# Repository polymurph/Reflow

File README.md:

# Reflow

## How to Contribute

source: https://www.youtube.com/watch?v=CML6vfKjQss

1. fork the project

2. make a new brachnch in the forked project

3. programm your features

3. one you are done go to your fork on github and hit the "compare & pull request" button

4. describe the feature, adaptation, bugfix or etc.

5. when done with documenting hit the "create pull request" button. 

## README Creation tipps

https://www.youtube.com/watch?v=E6NO0rgFub4

## Git Submodules

source: https://devconnected.com/how-to-add-and-update-git-submodules/

### Adding git submodule¨

-> https://stackoverflow.com/questions/43761594/cmake-and-using-git-submodule-for-dependence-projects

```
git submodule add <remote_url> <destination_folder>
git commit -m "Added the submodule to the project."
git push
```

### update git submodule

```
git submodule update --init --recursive
```

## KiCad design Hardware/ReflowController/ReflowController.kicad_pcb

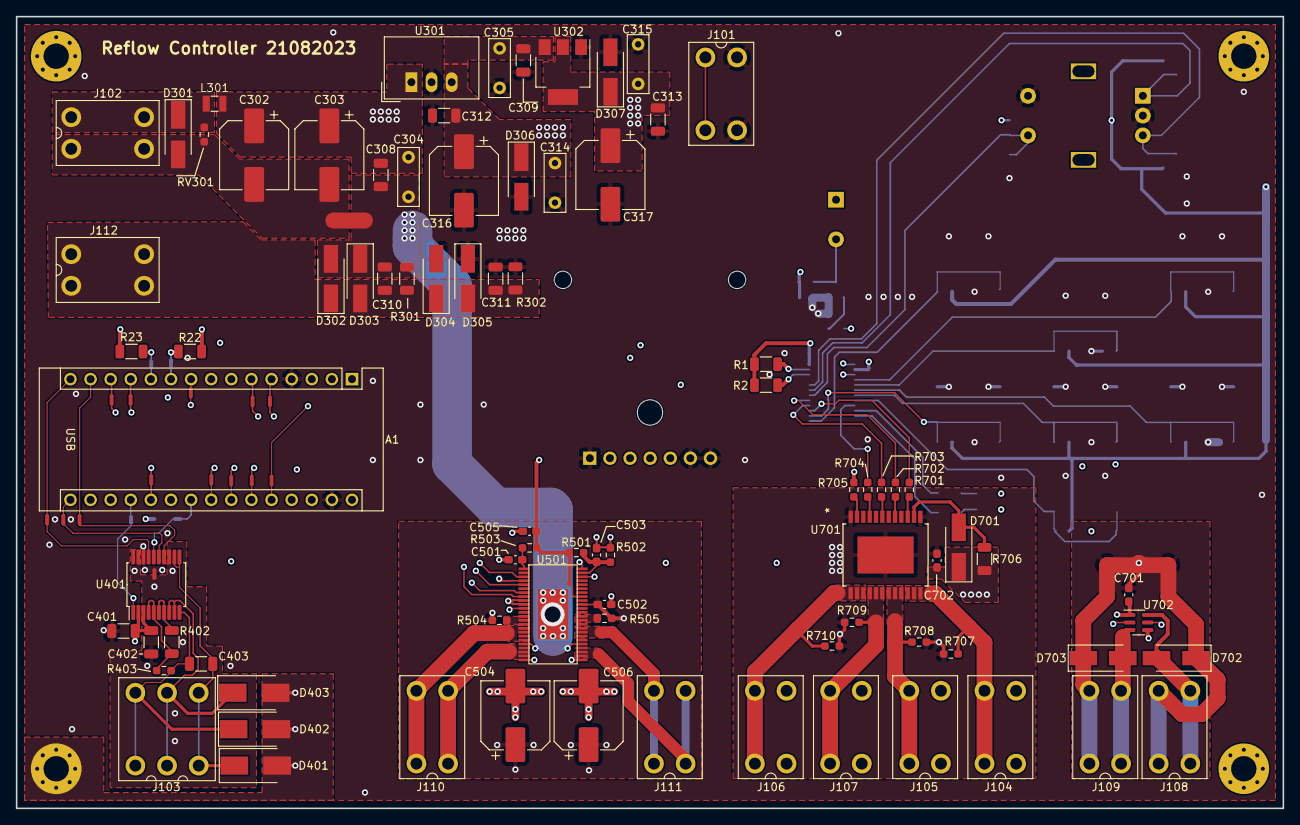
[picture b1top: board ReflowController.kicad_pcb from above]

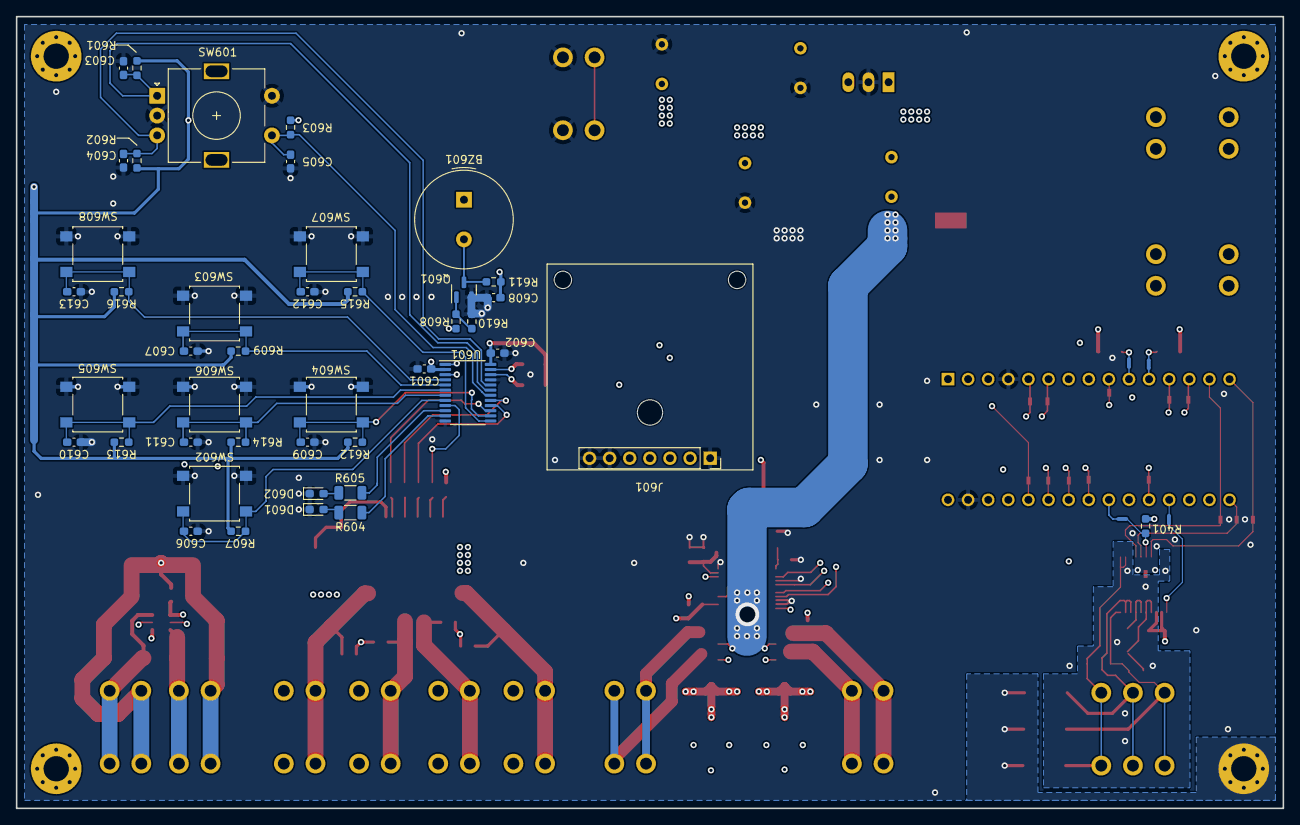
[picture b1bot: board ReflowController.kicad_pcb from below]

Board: 4 copper layers, 160.0 x 100.0 mm, 153 parts (47 on the bottom side), 90 nets.

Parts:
A1: NUCLEO_STM32F042K6; Arduino_Nano
BZ601: Buzzer; Buzzer_TDK_PS1240P02BT_D12.2mm_H6.5mm
C302, C303, C316, C317, C504, C506: 100uF; CP_Elec_8x10.5
C304, C305, C314, C315: 0.1uF; C_Rect_L7.2mm_W2.5mm_P5.00mm_FKS2_FKP2_MKS2_MKP2
C308, C309, C310, C311, C312, C313, C401, C402: 0.1uF; C_1206_3216Metric
C403: 10n; C_1206_3216Metric
C501: 270pF; C_0603_1608Metric_Pad1.08x0.95mm_HandSolder
C502, C503, C505, C601, C602, C603, C604, C605, C606, C607, C608, C609, C610, C611, C612, C613, C701, C702: 0.1uF; C_0603_1608Metric_Pad1.08x0.95mm_HandSolder
D301, D302, D303, D304, D305, D306, D307, D702, D703: SBRT; D_SMA_Handsoldering
D401, D402, D403: SMLVT3V3; D_SMB_Handsoldering
D601: RED; LED_0603_1608Metric_Pad1.05x0.95mm_HandSolder
D602: GREEN; LED_0603_1608Metric_Pad1.05x0.95mm_HandSolder
D701: RSFJL; D_SMA_Handsoldering
H101, H102, H103, H104: Mount; MountingHole_3.2mm_M3_Pad_Via
H105: Mount; MountingHole_3.2mm_M3
H106, H107: LCD_Mount; MountingHole_2.2mm_M2_ISO7380
J101, J102, J104, J105, J106, J107, J108, J109, J110, J111, J112: 2060-1452; wago_2060-1452
J103: 2060-1453; wago_2060-1453
J601: LCD_HEADER; PinSocket_1x07_P2.54mm_Vertical
L301: 470nH; 2520
NT1, NT2, NT3, NT4, NT5, NT6, NT7, NT8, NT9, NT10, NT11, NT12, NT13, NT14, NT15, NT16, NT17, NT402: NetTie_2; NetTie-2_SMD_Pad0.5mm
NT301, NT701, NT702: NetTie_2; NetTie-2_SMD_Pad2.0mm
Q601: BC848; SOT-23
R1, R2, R22, R23, R604, R605: 4k7; R_1206_3216Metric
R301, R302: 10M; R_1206_3216Metric
R401, R501, R502, R601, R602, R603, R607, R609, R610, R612, R613, R614, R615, R616, R701, R702, R703, R704, R705, R707, R708, R709, R710: 10k; R_0603_1608Metric_Pad0.98x0.95mm_HandSolder
R402: 402; R_1206_3216Metric
R403: 10M; R_0603_1608Metric_Pad0.98x0.95mm_HandSolder
R503: 5.1K; R_0603_1608Metric_Pad0.98x0.95mm_HandSolder
R504, R505: 0.22R; R_0603_1608Metric_Pad0.98x0.95mm_HandSolder
R608, R611: 1k; R_0603_1608Metric_Pad0.98x0.95mm_HandSolder
R706: 0R; R_1206_3216Metric
RV301: AVR; R_0603_1608Metric_Pad0.98x0.95mm_HandSolder
SW601: RotaryEncoder_Switch; RotaryEncoder_Alps_EC11E-Switch_Vertical_H20mm
SW602: SW_UP; SW_SPST_B3S-1000
SW603: SW_DOWN; SW_SPST_B3S-1000
SW604: SW_LEFT; SW_SPST_B3S-1000
SW605: SW_RIGHT; SW_SPST_B3S-1000
SW606: SW_SELECT; SW_SPST_B3S-1000
SW607: SW_RET; SW_SPST_B3S-1000
SW608: SW_RESET; SW_SPST_B3S-1000
U301: TSR_1-2450; Converter_DCDC_TRACO_TSR-1_THT
U302: LD1117S33TR_SOT223; SOT-223-3_TabPin2
U401: MAX31865xAP; SSOP-20_5.3x7.2mm_P0.65mm
U501: TB67H400AFNG; HTSSOP48
U601: PI4IOE5V6416; TSSOP-24_4.4x7.8mm_P0.65mm
U701: VNQ5160K-E
U702: SZNUD3124DMT1G; SC-74-6_1.5x2.9mm_P0.95mm

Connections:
+3.3V: A1.17 (3V3), BZ601.1 (-), C313.2, C315.1, C317.1, C401.2, C402.1, C601.1, C602.1, C608.1, D307.1 (K), J601.2, R1.1, R2.1, R22.1, R23.1, R401.2, R601.2, R602.1, R603.2, R607.2, R609.2, R611.1, R612.2, R613.2, R614.2, R615.2, R616.2, R705.2, U302.2 (VO), U401.2 (DVDD), U401.3 (VDD), U601.2 (VDD), U601.24 (VDDP)
+5V: A1.27 (+5V), C305.1, C309.2, C312.2, C314.1, C316.1, C505.1, D306.1 (K), R501.2, R503.2, U301.3 (Vout), U302.3 (VI), U501.41 (VCC)
+24V: C302.1, C303.1, C304.1, C308.2, C502.1, C504.1, C506.1, C701.1, C702.1, L301.2, NT701.1, NT702.1, R504.2, R505.2, R707.2, R708.2, R709.2, R710.2, U301.1 (Vin), U501.39 (VM), U701.1 (VCC), U701.12 (VCC), U701.EPAD (VCC)
/BUZZER_PWM: NT6.2, R608.1
/FAN_1_EN: NT12.2, U501.3 (INA1)
/FAN_1_PWM: NT13.2, U501.5 (PWMA)
/FAN_2_EN: NT14.2, U501.8 (INB1)
/FAN_2_PWM: NT15.2, U501.7 (PWMB)
/Fan Driver/FAN_1_OUT_+: J110.1, U501.16 (OUTA+), U501.17 (OUTA+)
/Fan Driver/FAN_1_OUT_-: J110.2, U501.22 (OUTA-), U501.23 (OUTA-)
/Fan Driver/FAN_2_OUT_+: J111.1, U501.32 (OUTB+), U501.33 (OUTB+)
/Fan Driver/FAN_2_OUT_-: J111.2, U501.26 (OUTB-), U501.27 (OUTB-)
/HSS_1_EN: R701.1, U601.15 (P1_2)
/HSS_2_EN: R703.1, U601.16 (P1_3)
/HSS_3_EN: R702.1, U601.17 (P1_4)
/HSS_4_EN: R704.1, U601.9 (P0_5)
/IO/HSS_1_OUT_+: J104.1, R707.1, U701.22 (OUTPUT1), U701.23 (OUTPUT1), U701.24 (OUTPUT1)
/IO/HSS_2_OUT_+: J105.1, R708.1, U701.19 (OUTPUT2), U701.20 (OUTPUT2), U701.21 (OUTPUT2)
/IO/HSS_3_OUT_+: J107.1, R709.1, U701.16 (OUTPUT3), U701.17 (OUTPUT3), U701.18 (OUTPUT3)
/IO/HSS_4_OUT_+: J106.1, R710.1, U701.13 (OUTPUT4), U701.14 (OUTPUT4), U701.15 (OUTPUT4)
/IO/relay_1_coil_+: D702.1 (K), J108.1, NT701.2
/IO/relay_1_coil_-: D702.2 (A), J108.2, U702.6 (Drain_1)
/IO/relay_2_coil_+: D703.1 (K), J109.1, NT702.2
/IO/relay_2_coil_-: D703.2 (A), J109.2, U702.3 (Drain_2)
/MISO: NT2.2, U401.17 (SDO)
/MOSI: NT1.2, U401.14 (SDI)
/PSU/24V_GND_IN: C302.2, C303.2, D301.2 (A), J102.2, NT301.1, RV301.2
/PSU/+24V_IN: D301.1 (K), J102.1, L301.1, RV301.1
/RELAY_1_EN: NT9.2, U702.2 (Gate_1)
/RELAY_2_EN: NT10.2, U702.5 (Gate_2)
/SCL: J601.3, NT5.2, R2.2, R23.2, U601.22 (SCL)
/SCLK: NT3.2, U401.15 (SCLK)
/SDA: J601.4, NT4.2, R1.2, R22.2, U601.23 (SDA)
/TemperatureReader/PT100_+IN: C403.2, D402.1 (K), J103.1, R403.1, U401.10 (RTDIN+)
/TemperatureReader/PT100_+OUT: D403.1 (K), J103.2, U401.8 (FORCE+), U401.9 (FORCE2)
/TemperatureReader/PT100_-IN: C403.1, D401.1 (K), J103.3, U401.11 (RTDIN-), U401.12 (FORCE-)
/TemperatureReader/REFIN+: R402.1, R403.2, U401.4 (BIAS), U401.5 (REFIN+)
/TemperatureReader/REFIN-: R402.2, U401.6 (REFIN-), U401.7 (ISENSOR)
/TemperatureReader/T_AGND: C402.2, NT402.2, U401.13 (GND), U401.19 (GND)
/uC/PA0: A1.19 (A0), NT16.1
/uC/PA1: A1.20 (A1), NT11.1
/uC/PA2: A1.26 (A7), NT8.1
/uC/PA4: A1.22 (A3), NT17.1
/uC/PA5: A1.23 (A4), NT6.1
/uC/PA6: A1.24 (A5), NT14.1
/uC/PA7: A1.25 (A6), NT12.1
/uC/PA8: A1.12 (D9), NT9.1
/uC/PA11: A1.13 (D10), NT10.1
/uC/PA12: A1.5 (D2), NT7.1
/uC/PB0: A1.6 (D3), NT13.1
/uC/PB1: A1.9 (D6), NT15.1
/uC/PB3: A1.16 (D13), NT3.1
/uC/PB4: A1.15 (D12), NT2.1
/uC/PB5: A1.14 (D11), NT1.1
/uC/PF0: A1.10 (D7), NT4.1
/uC/PF1: A1.11 (D8), NT5.1
/uC/~INT_EMERGENCY_STOP: J101.2, NT8.2
/ui/BTN_DOWN: C607.1, R609.1, SW603.2, U601.5 (P0_1)
/ui/BTN_LEFT: C609.1, R612.1, SW604.2, U601.14 (P1_1)
/ui/BTN_RESET: C613.1, R616.1, SW608.2, U601.4 (P0_0)
/ui/BTN_RET: C612.1, R615.1, SW607.2, U601.13 (P1_0)
/ui/BTN_RIGHT: C610.1, R613.1, SW605.2, U601.6 (P0_2)
/ui/BTN_SELECT: C611.1, R614.1, SW606.2, U601.7 (P0_3)
/ui/BTN_UP: C606.1, R607.1, SW602.2, U601.8 (P0_4)
/ui/ENCODER_A: C603.1, R601.1, SW601.A, U601.19 (P1_6)
/ui/ENCODER_B: C604.1, R602.2, SW601.B, U601.20 (P1_7)
/ui/ENCODER_SW: C605.1, R603.1, SW601.S1, U601.18 (P1_5)
/ui/LED_ALIVE: R605.1, U601.10 (P0_6)
/ui/LED_ERROR: R604.1, U601.11 (P0_7)
/~CS_TEMP: NT17.2, R401.1, U401.16 (~CS)
/~IO_INT: NT11.2, U601.1 (~INT)
/~TMP_RDY: NT16.2, U401.1 (~DRDY)
/~UI_RESET: J601.5, NT7.2, U601.3 (~RESET)
Earth: C310.1, C311.1, D302.1 (K), D303.2 (A), D304.1 (K), D305.2 (A), D401.2 (A), D402.2 (A), D403.2 (A), H101.1, H102.1, J112.1, J112.2, R301.2, R302.2
GND: A1.4 (GND), A1.29 (GND), C305.2, C309.1, C311.2, C312.1, C313.1, C314.2, C315.2, C316.2, C317.2, C401.1, C501.2, C503.2, C505.2, C601.2, C602.2, C603.2, C604.2, C605.2, C606.2, C607.2, C608.2, C609.2, C610.2, C611.2, C612.2, C613.2, D304.2 (A), D305.1 (K), D306.2 (A), D307.2 (A), D601.1 (K), D602.1 (K), J101.1, J601.1, J601.6, J601.7, NT402.1, Q601.2 (E), R302.1, R502.1, R610.1, SW601.C, SW601.S2, SW602.1, SW603.1, SW604.1, SW605.1, SW606.1, SW607.1, SW608.1, U301.2 (GND), U302.1 (GND), U401.18 (DGND), U501.4 (INA2), U501.9 (INB2), U501.10 (TBLKAB), U501.48 (HBMODE), U601.12 (VSS), U601.21 (ADDR)
GNDPWR: C304.2, C308.1, C310.2, C502.2, C504.2, C506.2, C701.2, C702.2, D302.2 (A), D303.1 (K), D701.1 (K), J104.2, J105.2, J106.2, J107.2, NT301.2, R301.1, R706.2, U501.11 (GND), U501.20 (GND), U501.24 (GND), U501.25 (GND), U501.29 (GND), U501.46 (GND), U501.PAD (GND), U702.1 (Source_1), U702.4 (Source_2)
unnamed: BZ601.2 (+), Q601.3 (C), R611.2
unnamed: D601.2 (A), R604.2
unnamed: D602.2 (A), R605.2
unnamed: D701.2 (A), R706.1, U701.2 (GND)
unnamed: Q601.1 (B), R608.2, R610.2
unnamed: R504.1, U501.13 (RSA), U501.14 (RSA)
unnamed: R505.1, U501.35 (RSB), U501.36 (RSB)
unnamed: C501.1, R503.1, U501.1 (OSCM)
unnamed: C503.1, R501.1, R502.2, U501.47 (VREF)
unnamed: R701.2, U701.3 (INPUT1)
unnamed: R702.2, U701.5 (INPUT2)
unnamed: R703.2, U701.7 (INPUT3)
unnamed: R704.2, U701.9 (INPUT4)
unnamed: R705.1, U701.11 (STAT_DIS)

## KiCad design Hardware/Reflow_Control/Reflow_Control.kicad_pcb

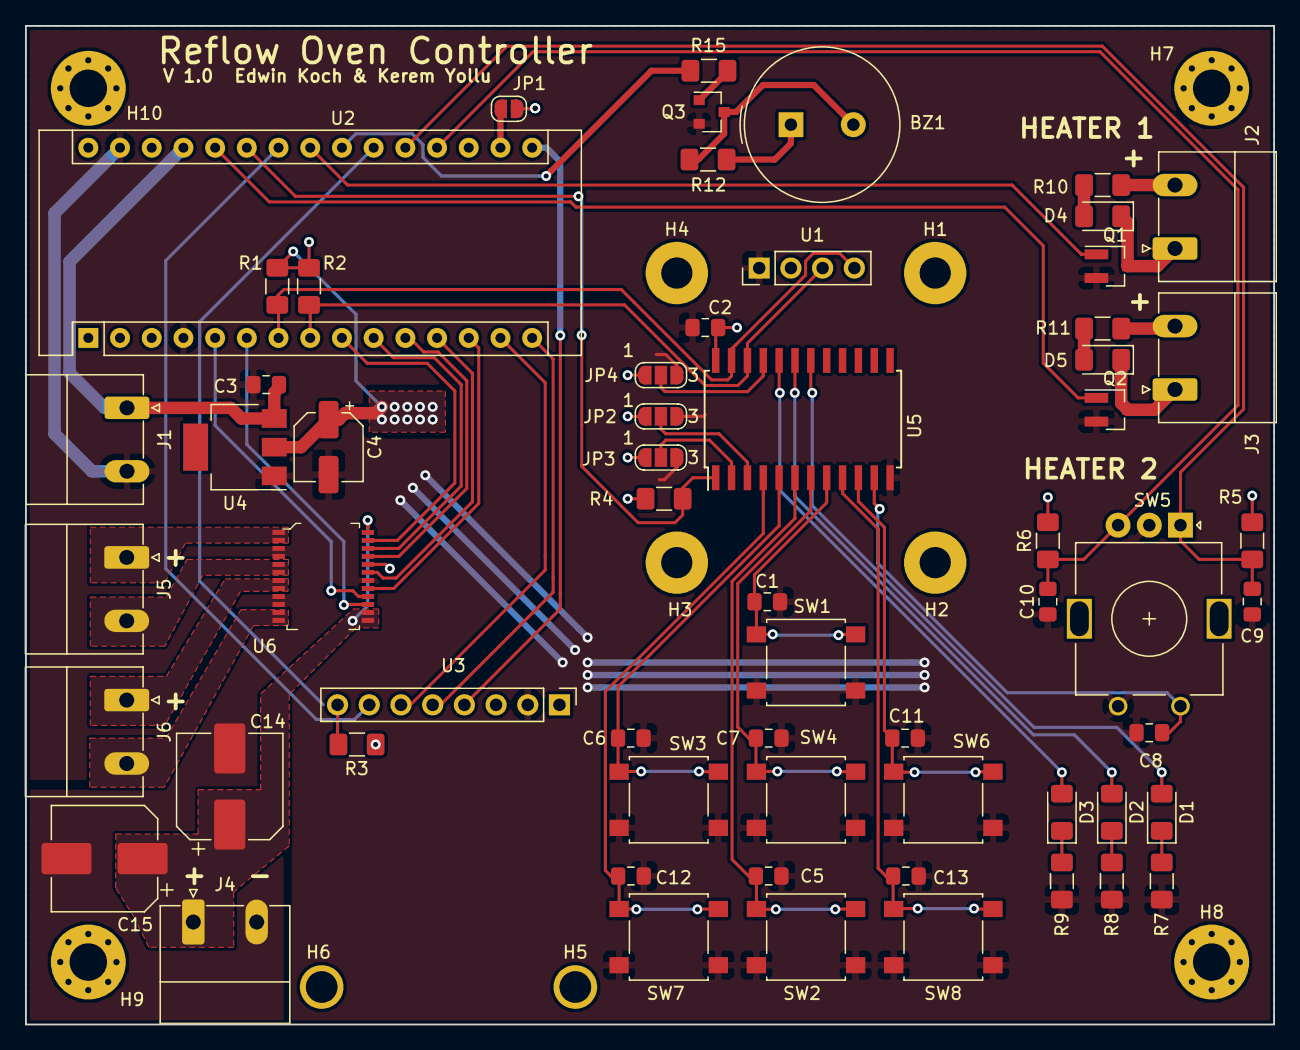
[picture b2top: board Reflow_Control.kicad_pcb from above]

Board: 2 copper layers, 100.0 x 80.0 mm, 71 parts (0 on the bottom side), 52 nets.

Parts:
BZ1: Buzzer; Buzzer_TDK_PS1240P02BT_D12.2mm_H6.5mm
C1, C3, C5, C6, C7, C8, C9, C10, C11, C12, C13: 10uF; C_0805_2012Metric_Pad1.15x1.40mm_HandSolder
C2: 100n; C_0805_2012Metric_Pad1.15x1.40mm_HandSolder
C4: 100uF; CP_Elec_5x5.4
C14, C15: 100uF; CP_Elec_8x6.2
D1, D2, D3, D4, D5: LED; LED_1206_3216Metric_Pad1.42x1.75mm_HandSolder
H1, H2, H3, H4, H5, H6: MountingHole; MountingHole_2.5mm_Pad
H7, H8, H9, H10: MountingHole; MountingHole_3mm_Pad_Via
J1: Conn_5V; PhoenixContact_MC_1,5_2-G-5.08_1x02_P5.08mm_Horizontal
J2: Conn_ssr_1; PhoenixContact_MC_1,5_2-G-5.08_1x02_P5.08mm_Horizontal
J3: Conn_ssr_2; PhoenixContact_MC_1,5_2-G-5.08_1x02_P5.08mm_Horizontal
J4: Conn_mot_PWR; PhoenixContact_MC_1,5_2-G-5.08_1x02_P5.08mm_Horizontal
J5: Conn_mot_1; PhoenixContact_MC_1,5_2-G-5.08_1x02_P5.08mm_Horizontal
J6: Conn_mot_2; PhoenixContact_MC_1,5_2-G-5.08_1x02_P5.08mm_Horizontal
JP1: 3.3V Jumper; SolderJumper-2_P1.3mm_Open_RoundedPad1.0x1.5mm
JP2, JP3, JP4: ADDR_A2; SolderJumper-3_P1.3mm_Open_RoundedPad1.0x1.5mm_NumberLabels
Q1: Q_NMOS_GSD; SOT-23_Handsoldering
Q2: NUD3112LT1G; SOT-23_Handsoldering
Q3: BC848; SOT-23
R1, R2, R3, R4, R5, R6, R7, R8, R9: 4k7; R_1206_3216Metric_Pad1.42x1.75mm_HandSolder
R10, R11, R12, R15: 1k; R_1206_3216Metric_Pad1.42x1.75mm_HandSolder
SW1, SW2, SW3, SW4, SW6, SW7, SW8: SW_Push; SW_SPST_B3S-1000
SW5: Rotary_Encoder_Switch; RotaryEncoder_Alps_EC11E_Vertical_H20mm
U1: SSD1306_128x64; PinHeader_1x04_P2.54mm_Vertical
U2: NUCLEO-F042K6; Arduino_Nano
U3: MAX31865_Breakout; PinHeader_1x08_P2.54mm_Vertical
U4: LM1117-3.3; SOT-223
U5: PCA9555; SOIC-24W_7.5x15.4mm_P1.27mm
U6: TB6612FNG_C_8_EL; LSSOP-24_W5.6mm

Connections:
+3V3: BZ1.1, C2.2, C4.1, J2.2, J3.2, JP1.2, JP2.1, JP3.1, JP4.1, R1.1, R2.1, R3.1, R4.1, R5.1, R6.1, R10.1, R11.1, R12.1, U1.2, U3.3, U4.2, U5.24, U6.20
+5V: C3.1, J1.1, U2.27, U4.3
/motor_vcc: C14.1, C15.1, J4.1, U6.13, U6.14, U6.24
ADDR_A0: JP4.2, U5.21
ADDR_A1: JP3.2, U5.2
ADDR_A2: JP2.2, U5.3
BTN_A: C12.1, SW7.1, U5.4
BTN_B: C13.1, SW8.1, U5.9
BTN_CENTER: C7.1, SW4.1, U5.7
BTN_DOWN: C5.1, SW2.1, U5.6
BTN_LEFT: C6.1, SW3.1, U5.5
BTN_RIGHT: C11.1, SW6.1, U5.10
BTN_UP: C1.1, SW1.1, U5.8
CH1_MOTOR_IN1: U2.11, U6.21
CH1_MOTOR_IN2: U2.10, U6.22
CH1_MOTOR_STBY: U2.12, U6.19
CH2_MOTOR_IN1: U2.5, U6.16
CH2_MOTOR_IN2: U2.13, U6.17
ENC_Switch: C8.2, SW5.S1, U5.11
GND: C1.2, C2.1, C3.2, C4.2, C5.2, C6.2, C7.2, C8.1, C9.1, C10.1, C11.2, C12.2, C13.2, C14.2, C15.2, J1.2, J4.2, JP2.3, JP3.3, JP4.3, Q1.2, Q2.2, Q3.2, R7.2, R8.2, R9.2, SW1.2, SW2.2, SW3.2, SW4.2, SW5.C, SW5.S2, SW6.2, SW7.2, SW8.2, U1.1, U2.4, U2.29, U3.2, U4.1, U5.12, U6.3, U6.4, U6.9, U6.10, U6.18
I2C1_SCL: R2.2, U1.3, U2.8, U5.22
I2C1_SDA: R1.2, U1.4, U2.7, U5.23
INT_ENC_A: C10.2, R6.2, SW5.B, U2.19
INT_ENC_B: C9.2, R5.2, SW5.A, U2.20
INT_MAX31865_RDY: R3.2, U2.21, U3.8
INT_PCA9555: R4.2, U2.25, U5.1
unnamed: BZ1.2, Q3.3, R12.2
unnamed: D1.1, R7.1
unnamed: D1.2, U5.18
unnamed: D2.1, R8.1
unnamed: D2.2, U5.19
unnamed: D3.1, R9.1
unnamed: D3.2, U5.20
unnamed: D4.1, J2.1, Q1.3
unnamed: D4.2, R10.2
unnamed: D5.1, J3.1, Q2.3
unnamed: D5.2, R11.2
unnamed: J5.1, U6.1, U6.2
unnamed: J5.2, U6.5, U6.6
unnamed: J6.1, U6.7, U6.8
unnamed: J6.2, U6.11, U6.12
unnamed: JP1.1, U2.17
unnamed: Q3.1, R15.1
SPI1_CS_MAX31865: U2.24, U3.7
SPI1_MISO: U2.15, U3.5
SPI1_MOSI: U2.14, U3.6
SPI1_SCK: U2.16, U3.4
SSR_1: Q1.1, U2.23
SSR_2: Q2.1, U2.26
TIM1_CH1_PWM_Buzzer: R15.2, U2.22
TIM3_CH1_MOTOR_PWM: U2.9, U6.23
TIM3_CH2_MOTOR_PWM: U2.6, U6.15

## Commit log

2022-03-06 added reflow pcb project v1.0
2022-03-06 added main.cpp
2022-03-06 created rough outline of project
2022-03-06 work onprojectstructure
2022-03-06 running crude project
2022-03-06 work on structure
2022-03-06 added single pattern notes and examples for the bsl layer
2022-12-27 pdate Readme.md
2022-12-27 moved all the old firmware to old/
2022-12-27 removed git submodule
2022-12-27 work on finite statemachine of the reflow oven
2022-12-27 work on reflowOven finite state machine structure
2022-12-27 updated .gitignore to ignore .vscode
2022-12-29 work on finite state machine
2022-12-31 working FSM example
2022-12-31 working on the temperature controller
2023-01-01 work on controller
2023-01-02 added stackoverflow link to git submodules
2023-01-02 addede cmake environment
2023-01-02 Added KED as submodule in Firmware
2023-01-02 updated .gitignore
2023-01-28 implemented KED as submodule and started with generic FSM
2023-02-11 Setting up the BSL layer for the reflow oven's hardware definitions and declarations
2023-02-11 Declared the oven object (typedef struct) and used it to init the board
2023-02-11 Added modules for the init of the refow oven's functionalities
2023-02-11 added old fsm from older commit -> 1e7ff9b75b226139d7d50fe2ad13ba92b39fc5dc
2023-02-11 work on README.md
2023-02-19 added PID class
2023-02-19 working on basic structure of the oven controller. Still does not compile!
2023-02-19 main.c cleanup
2023-02-19 working on structure
2023-03-21 renamed variable
2023-03-21 started work on the modules api
2023-04-09 created new reflow HW platform + started with block circuit
2023-04-10 work on uC
2023-04-12 defined rough structure with kerem
2023-04-12 started with schematic
2023-04-13 IMplemented the relay driver and High side switch. For the HSS there are some values to be caculated to enhance safety measures if we decide to implment them
2023-04-13 work on temp ic circuit
2023-04-13 Chnaged fan conroller
2023-04-14 Finished the fan controllers calculations, added the wago connectors, added notes
2023-04-14 Added the IO expander and RJ45 Connectors for LCD and Keypad Connectors
2023-04-15 work on MAX31865 circuit
2023-04-15 work on schematic
2023-04-15 work on circuit
2023-04-15 updated main schematic with kerem
2023-04-15 modifed gitignore
2023-04-15 finished the io control for the pcb, need to define what is the best way for a remote keypad
2023-04-16 Wrking with edwin on the hwole schematic
2023-04-16 Main Schematic rooting and PSU Dqsing ongoing
2023-04-17 Finished the desing of the PSUand started with the PCB TODO: missing fuse find a solution
2023-04-17 Continuing on the PCB coorected some pins from the MCU
2023-04-18 Made some progress on the PCB desgin for now only the main blocks are complete, thw pin connection of the mCU should be organised and Net-ties are making life much harder as you cant put them on the 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
2023-04-19 Advancing on the pcb removed netties from MCU
2023-04-19 work on uC schematic
2023-04-20 changed the uC schematic from the uC branch
2023-04-20 added the schematic of the updated pwerAndUi branch(with uC schematic update
2023-04-29 work on uC circuit. pin selection for the different IOs still pending
2023-05-06 work on pin assignment and porttable
2023-05-14 work on port table
2023-05-14 work on io adaption
2023-05-14 changed port table + updated schema
2023-05-16 work on porttable and on layout of temperature sensor
2023-05-18 work on layout of power
2023-05-18 work on layout
2023-05-20 Started layout with Edwin
2023-06-04 work on the lyout
2023-06-14 work on +24V power
2023-06-17 wotk on on power and ground
2023-07-18 work on the layout
2023-08-06 work on lyout
2023-08-15 work on laout
2023-08-19 working on DRC
2023-08-20 work on DRC
2023-08-20 Finished rewiev with Edwin, Need TO connect he HSS and DO the labeling
2023-08-21 work on completion for first proto
2023-09-09 created ibom html
2023-09-09 work on BOM cleanup

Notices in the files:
parts and their libraries:
Copyright 2016 Accelerated Designs. All rights reserved.
